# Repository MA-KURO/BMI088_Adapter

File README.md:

# BMI088_Adapter
BMI088转接板，引出所需接口

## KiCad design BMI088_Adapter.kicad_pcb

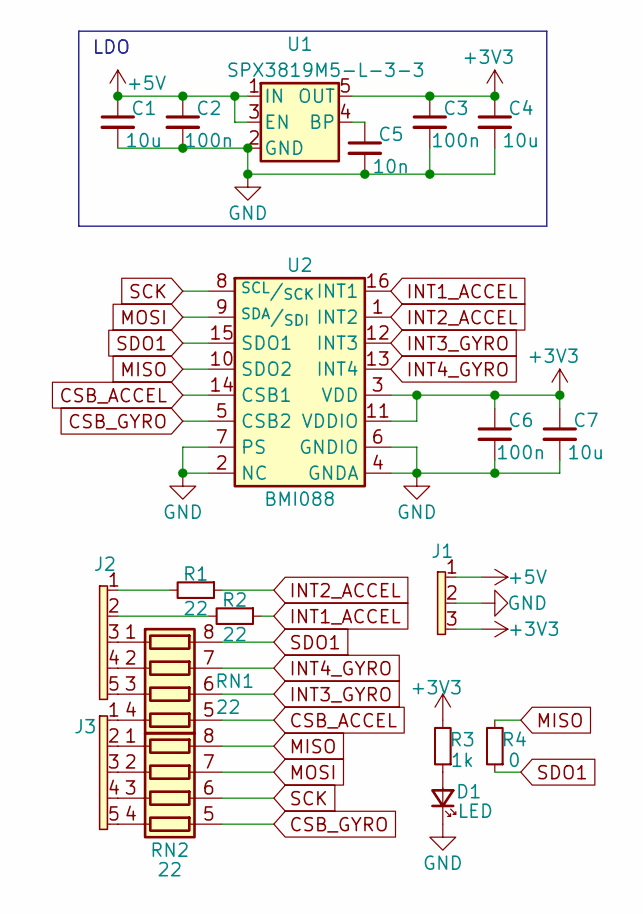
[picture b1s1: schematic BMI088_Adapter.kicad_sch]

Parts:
C1, C4, C7: 10u; 0603_C
C2, C3, C6: 100n; 0603_C
C5: 10n; 0603_C
D1: LED; 0603_D
J1: Conn_01x03_Pin_N; PinHeader_1x03_P2.54mm_Vertical
J2, J3: Conn_01x05_Pin_N; PinHeader_1x05_P2.54mm_Vertical
R1, R2: 22; 0603_R
R3: 1k; 0603_R
R4: 0; 0603_R
RN1, RN2: 22; 0603_RX4
U1: SPX3819M5-L-3-3; SOT-23-5
U2: BMI088; LGA-16_L4.5_W3.0_P0.50_ClockwisePinNumbering

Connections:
+3V3: C3.1, C4.1, C6.1, C7.1, J1.3, R3.2, U1.5 (OUT), U2.3 (VDD), U2.11 (VDDIO)
+5V: C1.1, C2.1, J1.1, U1.1 (IN), U1.3 (EN)
CSB_ACCEL: RN1.5 (R4.2), U2.14 (CSB1)
CSB_GYRO: RN2.5 (R4.2), U2.5 (CSB2)
GND: C1.2, C2.2, C3.2, C4.2, C5.2, C6.2, C7.2, D1.2 (K), J1.2, U1.2 (GND), U2.2 (NC), U2.4 (GNDA), U2.6 (GNDIO), U2.7 (PS)
INT1_ACCEL: R2.1, U2.16 (INT1)
INT2_ACCEL: R1.1, U2.1 (INT2)
INT3_GYRO: RN1.6 (R3.2), U2.12 (INT3)
INT4_GYRO: RN1.7 (R2.2), U2.13 (INT4)
MISO: R4.2, RN2.8 (R1.2), U2.10 (SDO2)
MOSI: RN2.7 (R2.2), U2.9 (^{SDA}/_{SDI})
unnamed: D1.1 (A), R3.1
unnamed: J2.1, R1.2
unnamed: J2.2, R2.2
unnamed: J2.3, RN1.1 (R1.1)
unnamed: J2.4, RN1.2 (R2.1)
unnamed: J2.5, RN1.3 (R3.1)
unnamed: J3.1, RN1.4 (R4.1)
unnamed: J3.2, RN2.1 (R1.1)
unnamed: J3.3, RN2.2 (R2.1)
unnamed: J3.4, RN2.3 (R3.1)
unnamed: J3.5, RN2.4 (R4.1)
unnamed: C5.1, U1.4 (BP)
SCK: RN2.6 (R3.2), U2.8 (^{SCL}/_{SCK})
SDO1: R4.1, RN1.8 (R1.2), U2.15 (SDO1)

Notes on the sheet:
LDO

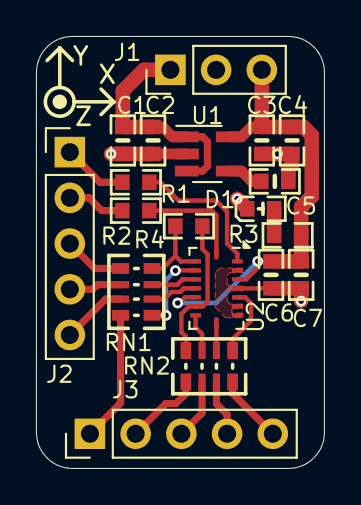
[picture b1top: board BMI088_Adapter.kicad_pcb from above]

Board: 2 copper layers, 16.0 x 24.0 mm, 19 parts (0 on the bottom side), 25 nets.

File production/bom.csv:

Designator,Footprint,Quantity,Value,LCSC Part #
"C1, C4, C7",0603_C,3,10u,
"C2, C3, C6",0603_C,3,100n,
C5,0603_C,1,10n,
D1,0603_D,1,LED,
J1,PinHeader_1x03_P2.54mm_Vertical,1,Conn_01x03_Pin_N,
"J2, J3",PinHeader_1x05_P2.54mm_Vertical,2,Conn_01x05_Pin_N,
"R1, R2",0603_R,2,22,
R3,0603_R,1,1k,
R4,0603_R,1,0,
"RN1, RN2",0603_RX4,2,22,
U1,SOT-23-5,1,SPX3819M5-L-3-3,
U2,LGA-16_L4.5_W3.0_P0.50_ClockwisePinNumbering,1,BMI088,

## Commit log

2024-06-06 第一次提交
2024-06-23 制造输出
